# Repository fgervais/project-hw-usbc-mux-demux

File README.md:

# USB-C mux/demux

## Use-cases

Basically used to mux or demux usb 2.0 data bus with USB-PD up to and including
revision 3.1 at 48V.

Here's an illustration highlighting a couple use-cases:

## Switching converter analysis

50 ohms series termination at the SW node.

### Switch node

| Input Voltage | Waveform | Rising edge |
|---------------|----------|-------------|
| 10V           |  |  |
| 20V           |  |  |
| 48V           |  |  |

### Output (5V)

| Input Voltage | No Load | 50 mA | 500 mA | 1 A |
|---------------|---------|-------|--------|-----|
| 10V           |  |  |  |  |
| 20V           |  |  |  |  |
| 48V           |  |  |  |  |

| Input Voltage | No Load | 50 mA | 500 mA | 1 A |
|---------------|---------|-------|--------|-----|
| 10V           |  |  |  |  |
| 20V           |  |  |  |  |
| 48V           |  |  |  |  |

### Noise

| Input Voltage | No Load | 50 mA | 500 mA | 1 A |
|---------------|---------|-------|--------|-----|
| 10V           | 17.60 mV (0.35%) | 19.80 mV (0.40%) | 13.00 mV (0.26%) | 12.40 mV (0.25%) |
| 20V           | 13.40 mV (0.27%) | 14.80 mV (0.30%) | 15.20 mV (0.30%) | 15.40 mV (0.31%) |
| 48V           | 15.00 mV (0.30%) | 17.60 mV (0.35%) | 28.20 mV (0.56%) | 19.60 mV (0.39%) |

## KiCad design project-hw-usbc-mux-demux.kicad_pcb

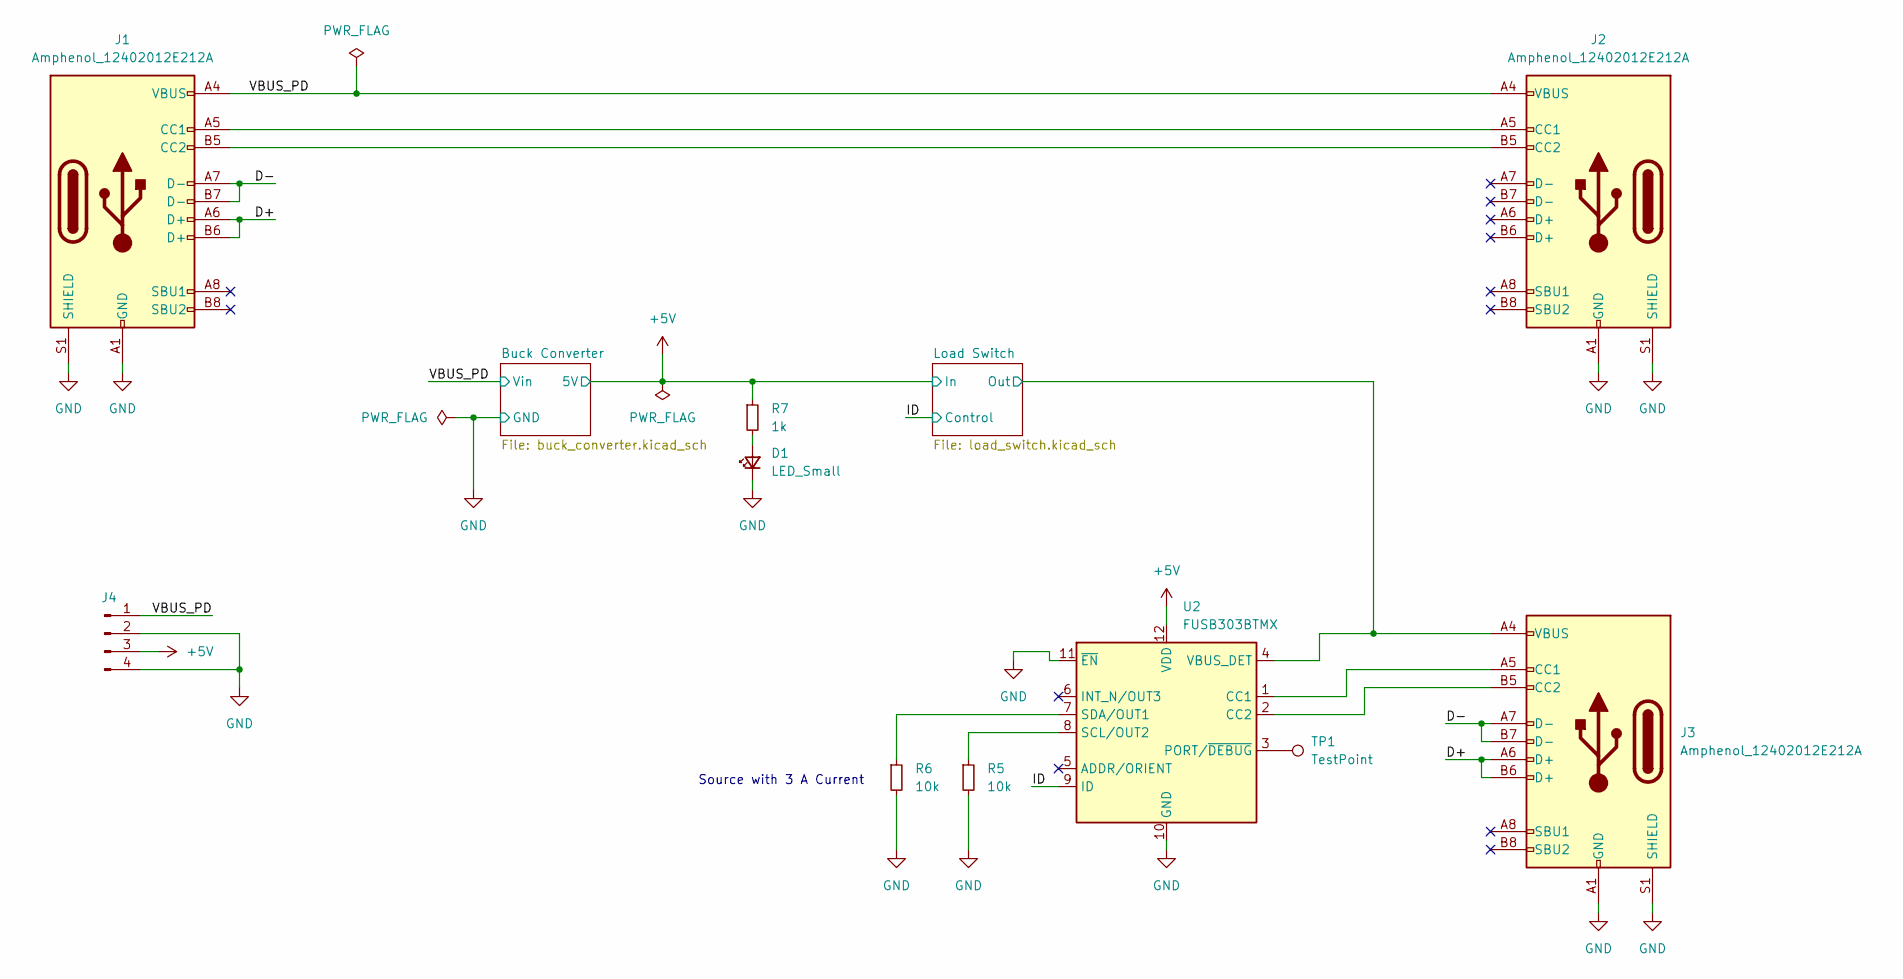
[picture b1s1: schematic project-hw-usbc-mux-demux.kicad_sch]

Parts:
D1: LED_Small; LED_0603_1608Metric
J1, J2, J3: Amphenol_12402012E212A
J4: Conn_01x04_Pin; PinHeader_1x04_P2.54mm_Vertical
R5, R6: 10k; R_0603_1608Metric
R7: 1k; R_0603_1608Metric
TP1: TestPoint; TestPoint_Pad_D1.0mm
U2: FUSB303BTMX; Texas_X2QFN-12_1.6x1.6mm_P0.4mm

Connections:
+5V: J4.3, R7.1, U2.12 (VDD); also elsewhere on the board
/D+: J1.A6 (D+), J1.B6 (D+), J3.A6 (D+), J3.B6 (D+)
/D-: J1.A7 (D-), J1.B7 (D-), J3.A7 (D-), J3.B7 (D-)
/ID: U2.9 (ID); also elsewhere on the board
/Load Switch/Out: J3.A4 (VBUS), J3.A9 (VBUS), J3.B4 (VBUS), J3.B9 (VBUS), U2.4 (VBUS_DET); also elsewhere on the board
/VBUS_PD: J1.A4 (VBUS), J1.A9 (VBUS), J1.B4 (VBUS), J1.B9 (VBUS), J2.A4 (VBUS), J2.A9 (VBUS), J2.B4 (VBUS), J2.B9 (VBUS), J4.1; also elsewhere on the board
GND: D1.1 (K), J1.A1 (GND), J1.A12 (GND), J1.B1 (GND), J1.B12 (GND), J1.S1 (SHIELD), J2.A1 (GND), J2.A12 (GND), J2.B1 (GND), J2.B12 (GND), J2.S1 (SHIELD), J3.A1 (GND), J3.A12 (GND), J3.B1 (GND), J3.B12 (GND), J3.S1 (SHIELD), J4.2, J4.4, R5.2, R6.2, U2.10 (GND), U2.11 (~EN); also elsewhere on the board
unnamed: D1.2 (A), R7.2
unnamed: J1.A5 (CC1), J2.A5 (CC1)
unnamed: J1.B5 (CC2), J2.B5 (CC2)
unnamed: J3.A5 (CC1), U2.1 (CC1)
unnamed: J3.B5 (CC2), U2.2 (CC2)
unnamed: TP1.1, U2.3 (PORT/~DEBUG)
unnamed: R5.1, U2.8 (SCL/OUT2)
unnamed: R6.1, U2.7 (SDA/OUT1)

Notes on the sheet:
Source with 3 A Current

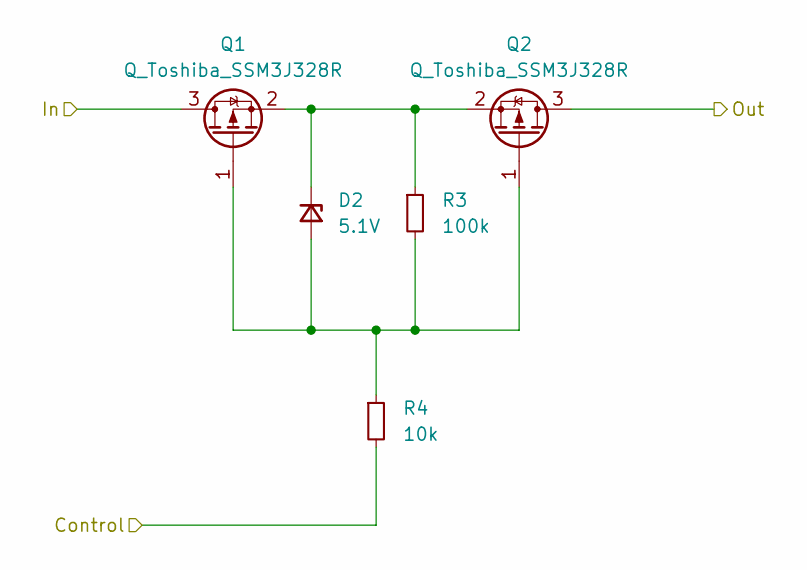
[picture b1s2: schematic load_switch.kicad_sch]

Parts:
D2: 5.1V; D_SOD-523
Q1, Q2: Q_Toshiba_SSM3J328R; SOT-23F
R3: 100k; R_0603_1608Metric
R4: 10k; R_0603_1608Metric

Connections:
+5V: Q1.3 (D); also elsewhere on the board
/ID: R4.2; also elsewhere on the board
/Load Switch/Out: Q2.3 (D); also elsewhere on the board
unnamed: D2.2 (A), Q1.1 (G), Q2.1 (G), R3.2, R4.1
unnamed: D2.1 (K), Q1.2 (S), Q2.2 (S), R3.1

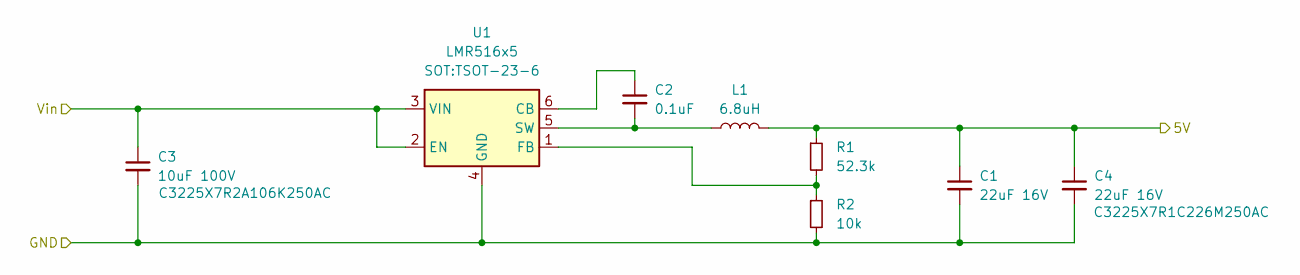
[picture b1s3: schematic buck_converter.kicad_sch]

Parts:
C1, C4: 22uF 16V; C_1210_3225Metric
C2: 0.1uF; C_0603_1608Metric
C3: 10uF 100V; C_1210_3225Metric
L1: 6.8uH; L_TDK_VLS6045EX_VLS6045AF
R1: 52.3k; R_0603_1608Metric
R2: 10k; R_0603_1608Metric
U1: LMR516x5; TSOT-23-6

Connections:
+5V: C1.1, C4.1, L1.2, R1.1; also elsewhere on the board
/VBUS_PD: C3.1, U1.2 (EN), U1.3 (VIN); also elsewhere on the board
GND: C1.2, C3.2, C4.2, R2.2, U1.4 (GND); also elsewhere on the board
unnamed: C2.1, U1.6 (CB)
unnamed: R1.2, R2.1, U1.1 (FB)
unnamed: C2.2, L1.1, U1.5 (SW)

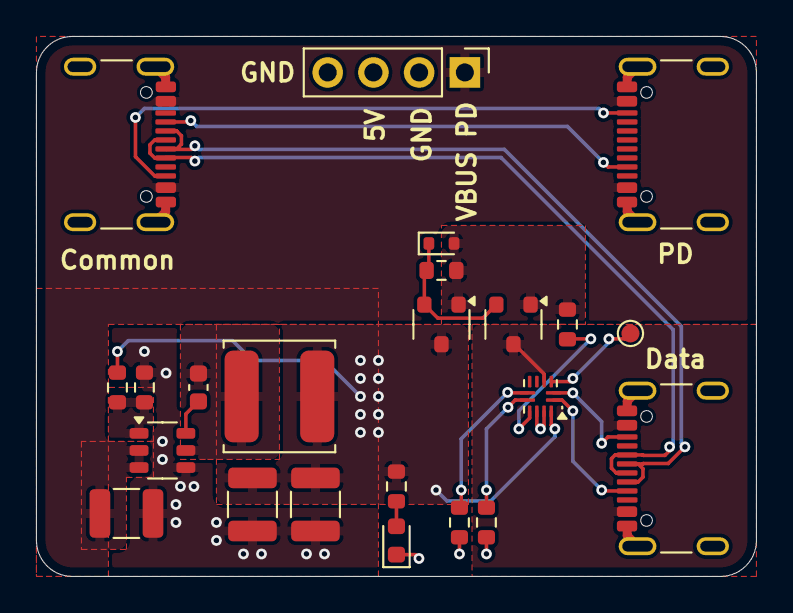
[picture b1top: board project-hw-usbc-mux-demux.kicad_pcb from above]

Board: 4 copper layers, 40.0 x 30.0 mm, 23 parts (0 on the bottom side), 20 nets.

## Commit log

2025-08-16 Add black kicad project
2025-08-16 sch: add buck converter
2025-08-17 sch: first draft
2025-08-20 sch: add zener diode
2025-08-20 sch: fix errors
2025-08-20 sch: add test point
2025-08-21 sch: add usb footprint
2025-08-21 sch: add power connectors
2025-08-21 pcb: route converter
2025-08-22 pcb: route most of the board
2025-08-22 pcb: first draft ready
2025-08-22 pcb: add silkscreen
2025-08-22 pcb: make pd poor wider
2025-08-22 pcb: add version
2025-08-22 pcb: add dragon logo
2025-08-23 pcb: hide header 3d model
2025-08-23 Add gerber files
2025-09-06 Add assembly file
2025-09-11 Update the README
2025-09-21 Add schematic file
2026-02-07 Add regulator analysis to README
2026-02-14 Add output analysis to README
2026-02-15 Add noise analysis to README
2026-03-28 README: add output setup image
